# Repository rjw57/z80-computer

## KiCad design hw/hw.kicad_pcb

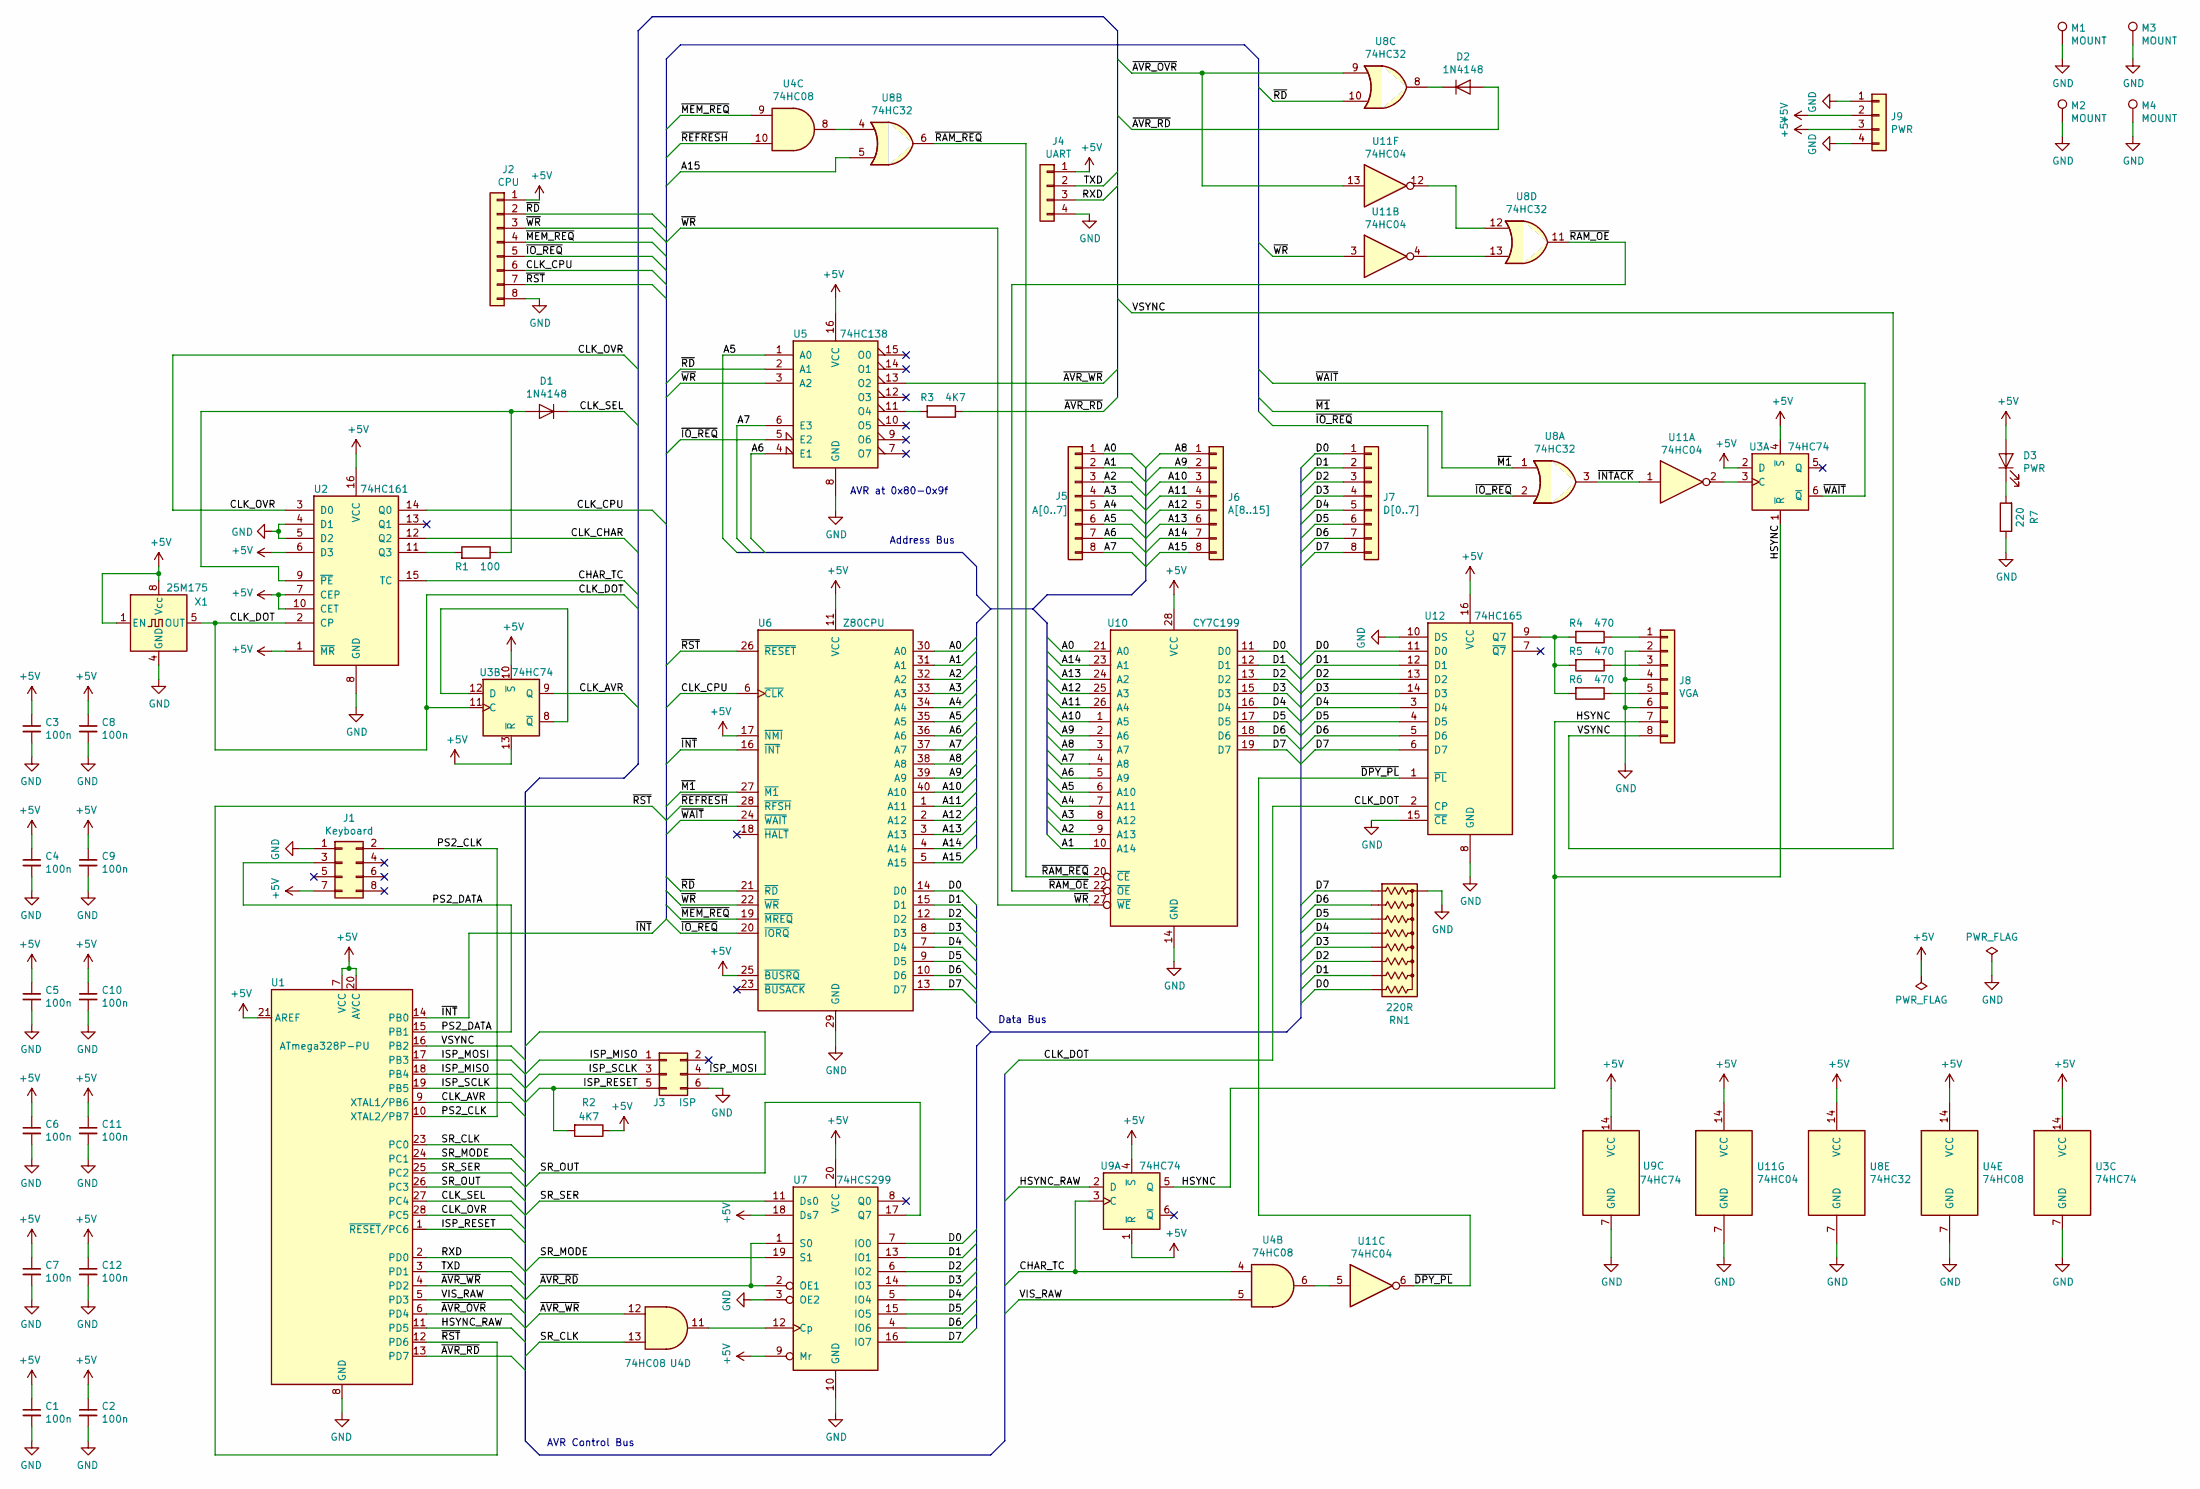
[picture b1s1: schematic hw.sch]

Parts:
C1, C2, C3, C4, C5, C6, C7, C8, C9, C10, C11, C12: 100n; C_Disc_D3.0mm_W2.0mm_P2.50mm
D1, D2: 1N4148; D_DO-35_SOD27_P7.62mm_Horizontal
D3: PWR; LED_D5.0mm
J1: Keyboard; PinHeader_2x04_P2.54mm_Vertical
J2: CPU; PinHeader_1x08_P2.54mm_Vertical
J3: ISP; PinHeader_2x03_P2.54mm_Vertical
J4: UART; PinHeader_1x04_P2.54mm_Vertical
J5: A[0..7]; PinHeader_1x08_P2.54mm_Vertical
J6: A[8..15]; PinHeader_1x08_P2.54mm_Vertical
J7: D[0..7]; PinHeader_1x08_P2.54mm_Vertical
J8: VGA; PinSocket_1x08_P2.54mm_Vertical
J9: PWR; PinHeader_1x04_P2.54mm_Vertical
M1, M2, M3, M4: MOUNT; MountingHole_3.5mm_Pad_Via
R1: 100; R_Axial_DIN0207_L6.3mm_D2.5mm_P7.62mm_Horizontal
R2, R3: 4K7; R_Axial_DIN0207_L6.3mm_D2.5mm_P7.62mm_Horizontal
R4, R5, R6: 470; R_Axial_DIN0207_L6.3mm_D2.5mm_P7.62mm_Horizontal
R7: 220; R_Axial_DIN0207_L6.3mm_D2.5mm_P7.62mm_Horizontal
RN1: 220R; R_Array_SIP9
U1: ATmega328P-PU; DIP-28_W7.62mm_Socket
U2: 74HC161; DIP-16_W7.62mm_Socket
U3, U9: 74HC74; DIP-14_W7.62mm_Socket
U4: 74HC08; DIP-14_W7.62mm_Socket
U5: 74HC138; DIP-16_W7.62mm_Socket
U6: Z80CPU; DIP-40_W15.24mm_Socket
U7: 74HCS299; DIP-20_W7.62mm_Socket
U8: 74HC32; DIP-14_W7.62mm_Socket
U10: CY7C199; DIP-28_W7.62mm_Socket
U11: 74HC04; DIP-14_W7.62mm_Socket
U12: 74HC165; DIP-16_W7.62mm_Socket
X1: 25M175; Oscillator_DIP-8

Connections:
+5V: C1.1, C2.1, C3.1, C4.1, C5.1, C6.1, C7.1, C8.1, C9.1, C10.1, C11.1, C12.1, D3.2 (A), J1.7, J2.1, J4.1, J9.2, J9.3, R2.1, U1.7 (VCC), U1.20 (AVCC), U1.21 (AREF), U2.1 (~MR), U2.6 (D3), U2.7 (CEP), U2.10 (CET), U2.16 (VCC), U3.2 (D), U3.4 (~S), U3.10 (~S), U3.13 (~R), U3.14 (VCC), U4.14 (VCC), U5.16 (VCC), U6.11 (VCC), U6.17 (~NMI~), U6.25 (~BUSRQ~), U7.9 (Mr), U7.18 (Ds7), U7.20 (VCC), U8.14 (VCC), U9.1 (~R), U9.4 (~S), U9.14 (VCC), U10.28 (VCC), U11.14 (VCC), U12.16 (VCC), X1.1 (EN), X1.8 (Vcc)
/A0: J5.1, U6.30 (A0), U10.21 (A0)
/A1: J5.2, U6.31 (A1), U10.10 (A14)
/A2: J5.3, U6.32 (A2), U10.9 (A13)
/A3: J5.4, U6.33 (A3), U10.8 (A12)
/A4: J5.5, U6.34 (A4), U10.7 (A11)
/A5: J5.6, U5.1 (A0), U6.35 (A5), U10.6 (A10)
/A6: J5.7, U5.4 (E1), U6.36 (A6), U10.5 (A9)
/A7: J5.8, U5.6 (E3), U6.37 (A7), U10.4 (A8)
/A8: J6.1, U6.38 (A8), U10.3 (A7)
/A9: J6.2, U6.39 (A9), U10.2 (A6)
/A10: J6.3, U6.40 (A10), U10.1 (A5)
/A11: J6.4, U6.1 (A11), U10.26 (A4)
/A12: J6.5, U6.2 (A12), U10.25 (A3)
/A13: J6.6, U6.3 (A13), U10.24 (A2)
/A14: J6.7, U6.4 (A14), U10.23 (A1)
/A15: J6.8, U6.5 (A15), U8.5
/CHAR_TC: U2.15 (TC), U4.4, U9.3 (C)
/CLK_AVR: U1.9 (XTAL1/PB6), U3.9 (Q)
/CLK_CPU: J2.6, U2.14 (Q0), U6.6 (~CLK~)
/CLK_DOT: U2.2 (CP), U3.11 (C), U12.2 (CP), X1.5 (OUT)
/CLK_OVR: U1.28 (PC5), U2.3 (D0)
/CLK_SEL: D1.1 (K), U1.27 (PC4)
/D0: J7.1, RN1.9 (R8), U6.14 (D0), U7.7 (IO0), U10.11 (D0), U12.11 (D0)
/D1: J7.2, RN1.8 (R7), U6.15 (D1), U7.13 (IO1), U10.12 (D1), U12.12 (D1)
/D2: J7.3, RN1.7 (R6), U6.12 (D2), U7.6 (IO2), U10.13 (D2), U12.13 (D2)
/D3: J7.4, RN1.6 (R5), U6.8 (D3), U7.14 (IO3), U10.15 (D3), U12.14 (D3)
/D4: J7.5, RN1.5 (R4), U6.7 (D4), U7.5 (IO4), U10.16 (D4), U12.3 (D4)
/D5: J7.6, RN1.4 (R3), U6.9 (D5), U7.15 (IO5), U10.17 (D5), U12.4 (D5)
/D6: J7.7, RN1.3 (R2), U6.10 (D6), U7.4 (IO6), U10.18 (D6), U12.5 (D6)
/D7: J7.8, RN1.2 (R1), U6.13 (D7), U7.16 (IO7), U10.19 (D7), U12.6 (D7)
/HSYNC: J8.7, U3.1 (~R), U9.5 (Q)
/HSYNC_RAW: U1.11 (PD5), U9.2 (D)
/ISP_MISO: J3.1, U1.18 (PB4)
/ISP_MOSI: J3.4, U1.17 (PB3)
/ISP_RESET: J3.5, R2.2, U1.1 (~RESET~/PC6)
/ISP_SCLK: J3.3, U1.19 (PB5)
/PS2_CLK: J1.2, U1.10 (XTAL2/PB7)
/PS2_DATA: J1.3, U1.15 (PB1)
/RXD: J4.3, U1.2 (PD0)
/SR_CLK: U1.23 (PC0), U4.13
/SR_MODE: U1.24 (PC1), U7.19 (S1)
/SR_OUT: U1.26 (PC3), U7.17 (Q7)
/SR_SER: U1.25 (PC2), U7.11 (Ds0)
/TXD: J4.2, U1.3 (PD1)
/VIS_RAW: U1.5 (PD3), U4.5
/VSYNC: J8.8, U1.16 (PB2)
/~AVR_OVR: U1.6 (PD4), U8.9, U11.13
/~AVR_RD: D2.2 (A), R3.1, U1.13 (PD7), U7.1 (S0), U7.2 (OE1)
/~AVR_WR: U1.4 (PD2), U4.12, U5.13 (O2)
/~DPY_PL: U11.6, U12.1 (~PL)
/~INT: U1.14 (PB0), U6.16 (~INT~)
/~INTACK: U8.3, U11.1
/~IO_REQ: J2.5, U5.5 (E2), U6.20 (~IORQ~), U8.2
/~M1: U6.27 (~M1~), U8.1
/~MEM_REQ: J2.4, U4.9, U6.19 (~MREQ~)
/~RAM_OE: U8.11, U10.22 (~OE~)
/~RAM_REQ: U8.6, U10.20 (~CE~)
/~RD: J2.2, U5.2 (A1), U6.21 (~RD~), U8.10
/~REFRESH: U4.10, U6.28 (~RFSH~)
/~RST: J2.7, U1.12 (PD6), U6.26 (~RESET~)
/~WAIT: U3.6 (~Q), U6.24 (~WAIT~)
/~WR: J2.3, U5.3 (A2), U6.22 (~WR~), U10.27 (~WE~), U11.3
GND: C1.2, C2.2, C3.2, C4.2, C5.2, C6.2, C7.2, C8.2, C9.2, C10.2, C11.2, C12.2, J1.1, J2.8, J3.6, J4.4, J8.2, J8.4, J8.6, J9.1, J9.4, M1.1, M2.1, M3.1, M4.1, R7.1, RN1.1 (common), U1.8 (GND), U1.22 (GND), U2.4 (D1), U2.5 (D2), U2.8 (GND), U3.7 (GND), U4.7 (GND), U5.8 (GND), U6.29 (GND), U7.3 (OE2), U7.10 (GND), U8.7 (GND), U9.7 (GND), U10.14 (GND), U11.7 (GND), U12.8 (GND), U12.10 (DS), U12.15 (~CE), X1.4 (GND)
unnamed: D1.2 (A), R1.1, U2.9 (~PE)
unnamed: D2.1 (K), U8.8
unnamed: D3.1 (K), R7.2
unnamed: J8.1, R4.1
unnamed: J8.3, R5.1
unnamed: J8.5, R6.1
unnamed: R1.2, U2.11 (Q3)
unnamed: R3.2, U5.11 (O4)
unnamed: R4.2, R5.2, R6.2, U12.9 (Q7)
unnamed: U3.8 (~Q), U3.12 (D)
unnamed: U4.8, U8.4
unnamed: U4.11, U7.12 (Cp)
unnamed: U3.3 (C), U11.2
unnamed: U8.13, U11.4
unnamed: U4.6, U11.5
unnamed: U8.12, U11.12

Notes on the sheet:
AVR at 0x80-0x9f
Address Bus
Data Bus
AVR Control Bus

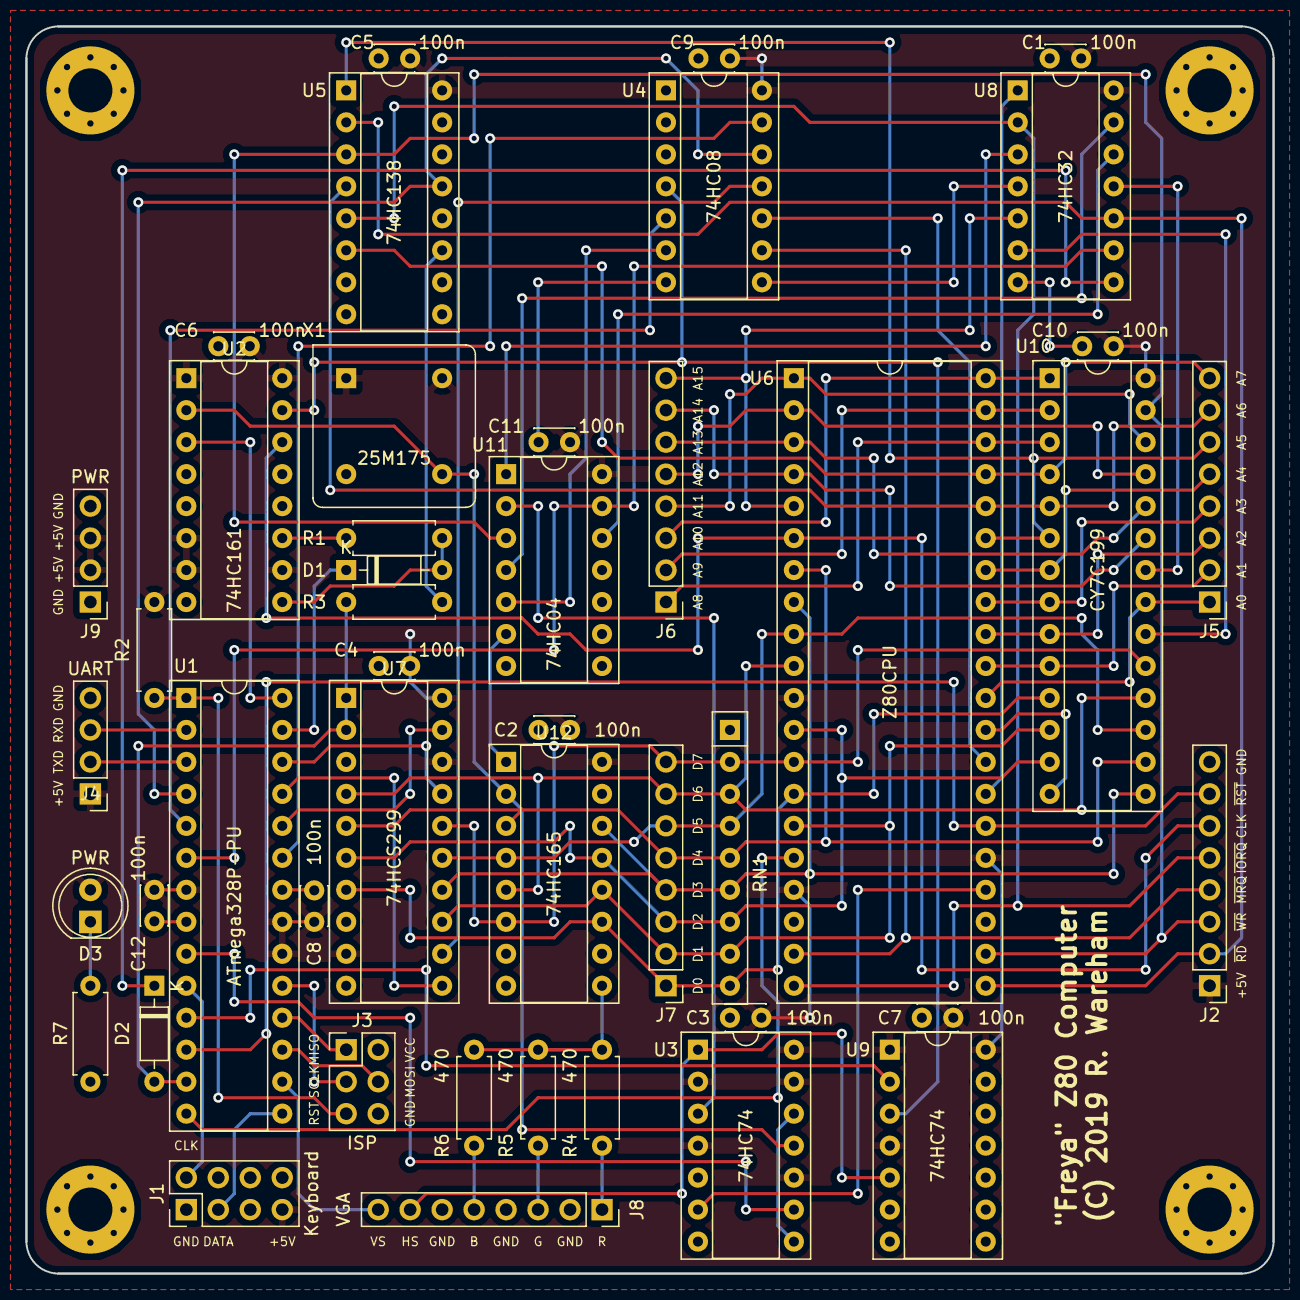
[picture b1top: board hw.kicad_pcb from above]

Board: 2 copper layers, 99.1 x 99.1 mm, 49 parts (0 on the bottom side), 80 nets.

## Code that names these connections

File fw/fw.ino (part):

#include <avr/pgmspace.h>

#define HSYNC           5 // =OC0B, fixed by hardware
#define VSYNC           10 // =OC1B, fixed by hardware
#define CHAR_CLK        4 // =T0, fixed by hardware

#define SR_SER          11
#define IO_ACK_BAR      9
#define SR_CLK          8
#define SR_MODE         7
#define SR_OUT          6

#define ARD_OVR_BAR     2
#define ARD_OVR         3
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#define RST_BAR         A5
#define CPU_RD_BAR      A4
#define CPU_INT_BAR     A3
#define CLK_SEL         A0
#define OV_CLK          A1

// RAM contents
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
  digitalWrite(SR_MODE, LOW); // shifting data

  // At this point the SR_OUT pin *already* has the MSB of the data bus on it so
  // don't reset the clock pin. That way shiftIn reads data after the *falling*
  // edge so we don't miss the MSB
  digitalWrite(SR_MODE, LOW); // read
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  //while (!Serial);  // wait for serial port to connect. Needed for native USB

  // Set HSYNC as output
  pinMode(HSYNC, OUTPUT);

  // Set VSYNC as output
  pinMode(VSYNC, OUTPUT);

  setup_timers();

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
  // Setup clock override pins
  pinMode(OV_CLK, OUTPUT);
  pinMode(CLK_SEL, OUTPUT);

  // Ensure we are the read device and set up data bus
  pinMode(SR_OUT, INPUT);
  digitalWrite(SR_SER, LOW);
  pinMode(SR_SER, OUTPUT);
  digitalWrite(SR_CLK, HIGH);
  pinMode(SR_CLK, OUTPUT);
  pinMode(ARD_OVR_BAR, OUTPUT);
  pinMode(ARD_OVR, OUTPUT);
  claim_read_dev();
  digitalWrite(SR_MODE, HIGH); // loading data
  pinMode(SR_MODE, OUTPUT);

  // Ensure CPU is in RESET state.
  digitalWrite(RST_BAR, LOW);
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
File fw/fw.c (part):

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volatile bool data_in_port = false;

// Set by pin change handler
volatile uint8_t ps2_data = 0;
volatile bool ps2_changed = true;

// CPU frequency is half the dot clock. Configure this and include delay header.
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  static uint8_t parity = 0;
  static uint16_t data = 0;

  ps2_clk = read_pin(PS2_CLK_PORT_NAME, PS2_CLK_PORT_BIT);

  // Read data on *falling* edge
  if((ps2_clk != prev_ps2_clock) && !ps2_clk) {
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  // already. However, the HSYNC pulse is not quite in the middle of the
  // inactive VIS region so we offset the inactive pulse from the HSYNC pulse.
  TCNT0 = 0;
  TCNT1 = 0; // corresponds to start of vsync pulse
  TCNT2 = 256-(int)(hvis_inactive_offset * timer_freq);

  // Enable OVF interrupt for timer 0
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
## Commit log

2019-06-23 add hline counter
2019-06-23 add stub OS
2019-06-23 add sram link
2019-06-23 add horiz intrerrupt
2019-06-23 start to get interrupts working
2019-06-30 tidy up fw
2019-07-07 start using a different way to initialise memory
2019-07-13 first version were OS gets copied in working
2019-07-13 add record of hardware
2019-07-13 WIP: start thinking how Arduino can respond to port requests
2019-07-14 got IO port writing working
2019-07-14 update schematic cache
2019-07-14 re-purpose IORQ as Arduino device output line and support read/write
2019-07-15 add output port
2019-07-15 partially isolate Arduino port
2019-07-20 add HSYNC and VSYNC signals
2019-07-20 add vertical sync interrupt
2019-07-21 start to generate video signal
2019-07-27 start to try and rationalise arduino port
2019-07-28 start hw rationalisation
2019-07-29 fix rationalised circuit
2019-07-31 start to get per character single pulse
2019-08-04 start to get video signal
2019-08-04 working video signal(!)
2019-08-05 getting there
2019-08-12 move over to dedicated AVR
2019-08-14 got video display working well
2019-08-14 finally got some semblance of checkerboard display
2019-08-15 get actual checkerboard pattern on screen!
2019-08-17 get text on screen
2019-08-18 got stable screen display and demo program
2019-08-18 fix schematic to match reality
2019-08-18 start to tidy up AVR to/from CPU comms
2019-08-18 move to BBC Micro font
2019-08-21 show only printable chars
2019-08-21 PS2 data reading and UART
2019-08-24 simplifying hw
2019-08-24 start schematic tidy up
2019-08-24 start schematic tidy up (more)
2019-08-24 finished first pass at schematic tidy up
2019-08-25 updated schematic to match prototype and checked it
2019-08-26 can actually type
2019-09-15 start PCB layout
2019-09-15 PCB now fully connected
2019-09-15 generate PCB output
2019-09-15 first PCB order

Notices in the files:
hw/hw.kicad_pcb:
(C) 2019 R. Wareham
